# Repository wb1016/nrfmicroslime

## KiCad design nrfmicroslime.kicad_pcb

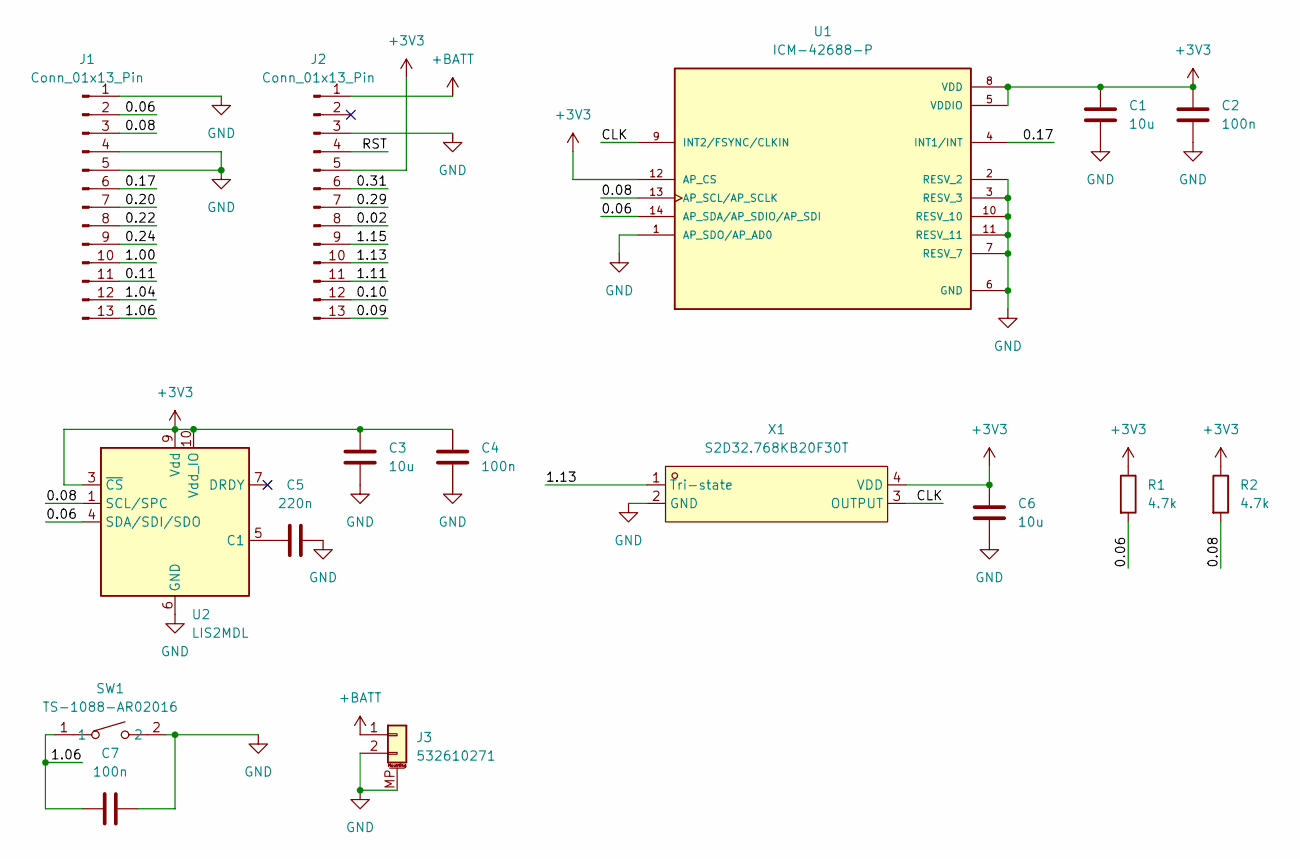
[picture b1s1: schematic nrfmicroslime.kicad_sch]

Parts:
C1, C3, C6: 10u; C_0402_1005Metric
C2, C4, C7: 100n; C_0402_1005Metric
C5: 220n; C_0402_1005Metric
J1, J2: Conn_01x13_Pin; PinHeader_1x13_P2.54mm_Vertical
J3: 532610271; Molex_PicoBlade_53261-0271_1x02-1MP_P1.25mm_Horizontal
R1, R2: 4.7k; R_0402_1005Metric
SW1: TS-1088-AR02016; SW-SMD_L3.9-W3.0-P4.45; LCSC Part C720477
U1: ICM-42688-P; PQFN50P300X250X97-14N; PARTREV 1.2
U2: LIS2MDL; LGA-12_2x2mm_P0.5mm
X1: S2D32.768KB20F30T; OSC-SMD_4P-L2.5-W2.0-BL; LCSC Part C387463

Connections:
+3V3: C1.1, C2.1, C3.1, C4.1, C6.1, J2.5, R1.1, R2.1, U1.5 (VDDIO), U1.8 (VDD), U1.12 (AP_CS), U2.3 (~CS), U2.9 (Vdd), U2.10 (Vdd_IO), X1.4 (VDD); also elsewhere on the board
+BATT: J2.1, J3.1
/0.02: J2.8
/0.08: J1.3, R2.2, U1.13 (AP_SCL/AP_SCLK), U2.1 (SCL/SPC)
/0.09: J2.13
/0.10: J2.12
/0.11: J1.11
/0.17: J1.6, U1.4 (INT1/INT)
/0.20: J1.7
/0.24: J1.9
/0.29: J2.7
/0.31: J2.6
/1.00: J1.10
/1.04: J1.12
/1.06: C7.1, J1.13, SW1.1
/1.11: J2.11
/1.13: J2.10, X1.1 (Tri-state)
/1.15: J2.9
/CLK: U1.9 (INT2/FSYNC/CLKIN), X1.3 (OUTPUT)
/RST: J2.4
GND: C1.2, C2.2, C3.2, C4.2, C5.2, C6.2, C7.2, J1.1, J1.4, J1.5, J2.3, J3.2, J3.MP (MountPin), SW1.2, U1.1 (AP_SDO/AP_AD0), U1.2 (RESV_2), U1.3 (RESV_3), U1.6 (GND), U1.7 (RESV_7), U1.10 (RESV_10), U1.11 (RESV_11), U2.6 (GND), U2.8 (GND), X1.2 (GND)
unnamed: C5.1, U2.5 (C1)

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
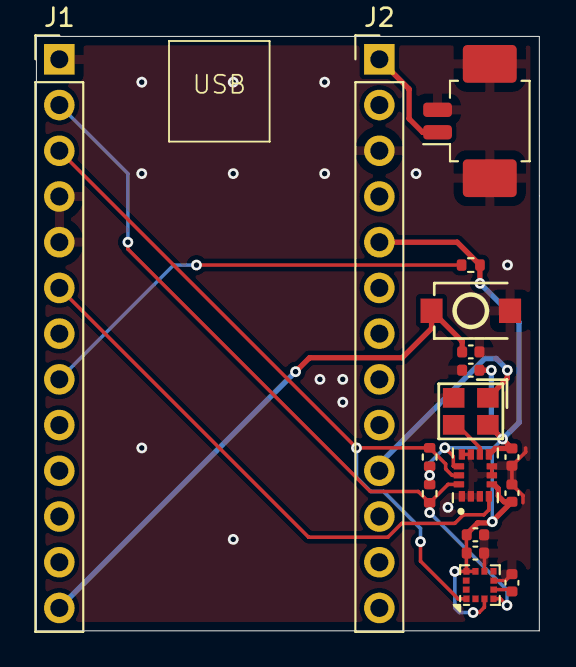
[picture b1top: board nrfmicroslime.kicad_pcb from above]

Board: 2 copper layers, 27.9 x 33.0 mm, 17 parts (0 on the bottom side), 11 nets.

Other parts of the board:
R1#2: 4.7k; R_0402_1005Metric

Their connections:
+3V3: R1#2.1; also elsewhere on the board

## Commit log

2024-09-13 narrower pcb, less components, pin configuration change
2024-09-13 add pngs
